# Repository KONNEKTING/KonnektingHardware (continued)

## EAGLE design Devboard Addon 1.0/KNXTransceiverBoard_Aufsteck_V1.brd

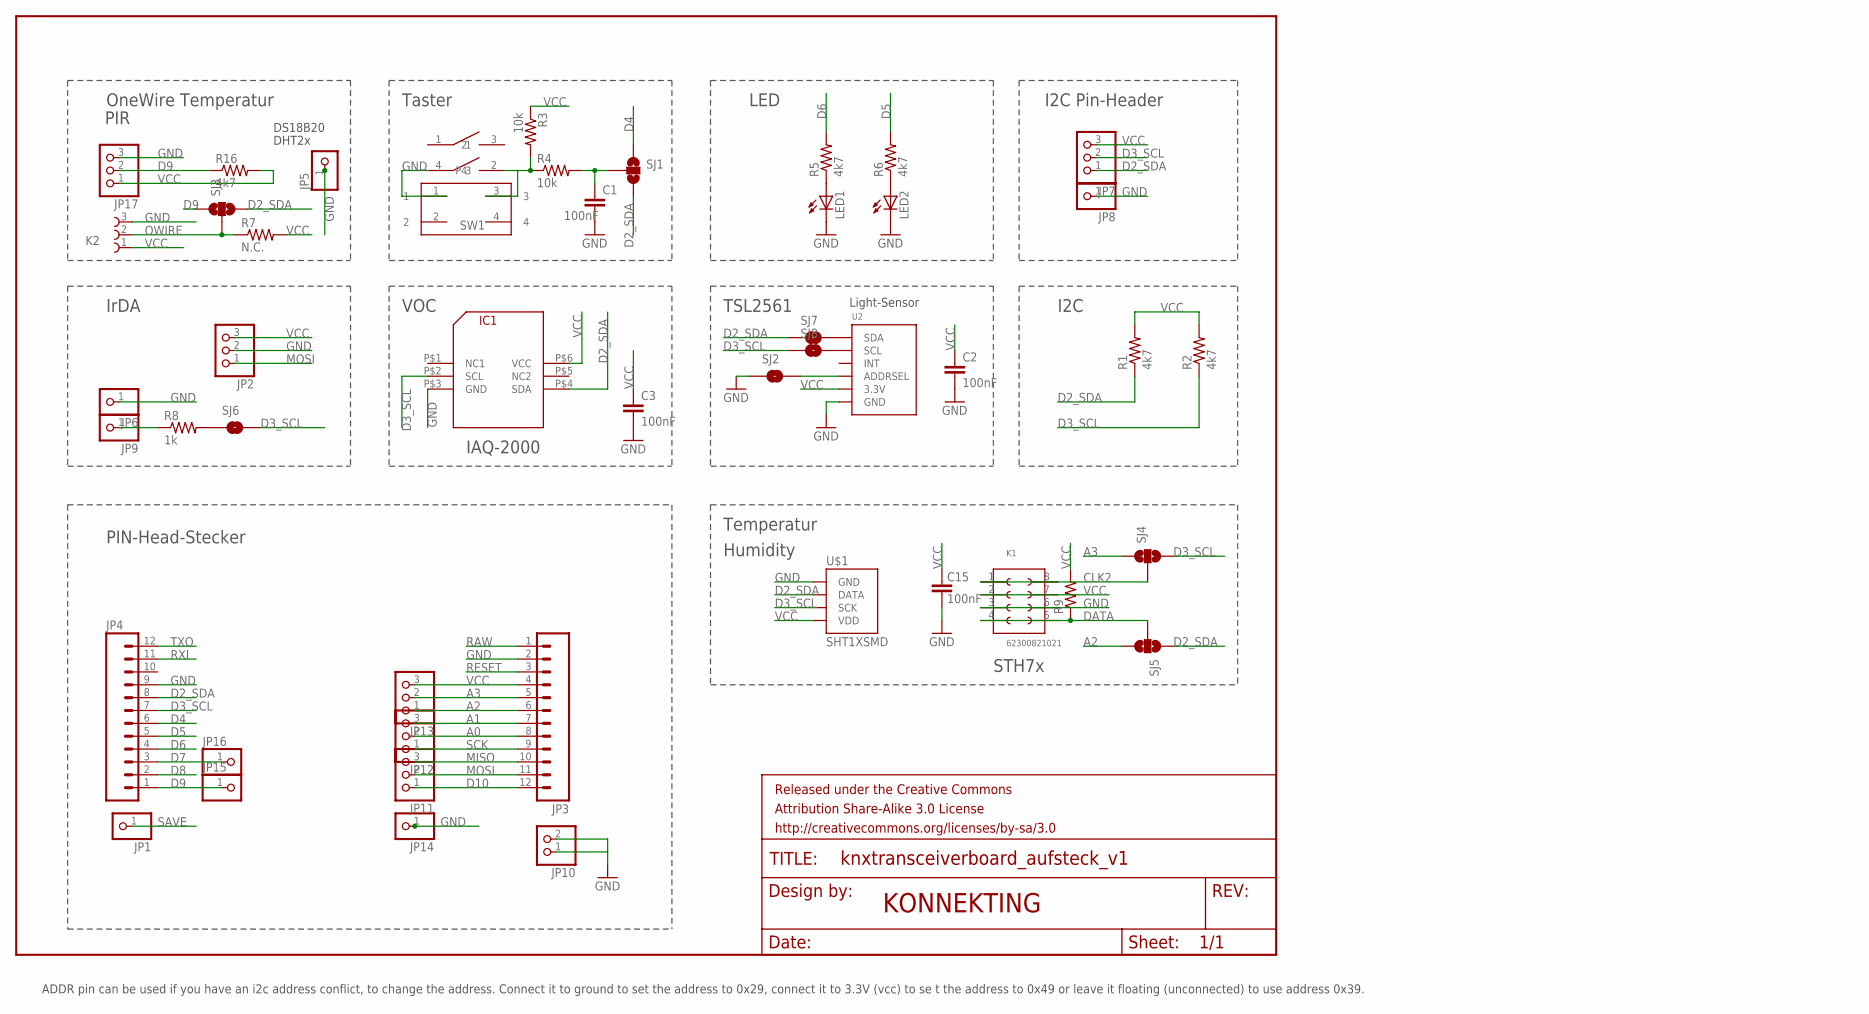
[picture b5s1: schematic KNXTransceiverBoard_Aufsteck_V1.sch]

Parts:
C1, C2, C3: 100nF; C0603
C15: 100nF; 0603-CAP
FRAME1: FRAME-LETTER; CREATIVE_COMMONS
IC1: AMSVOC
JP1, JP5, JP6, JP8, JP9, JP14, JP15, JP16: PINHD-1X1; 1X01
JP2, JP7, JP11, JP12, JP13, JP17: PINHD-1X3; 1X03
JP3, JP4: M12PTH; 1X12
JP10: PINHD-1X2; 1X02
K1: 62300821021
K2: 691101710003
LED1, LED2: LEDCHIPLED_0805; CHIPLED_0805
R1, R2, R5, R6, R16: 4k7; 0603-RES
R3, R4: 10k; 0603-RES
R7: N.C.; 0603-RES
R8: 1k; 0603-RES
R9: RESISTOR0603-RES; 0603-RES
SJ1, SJ3, SJ4, SJ5: SOLDERJUMPER_2WAY-OLDS; SJ_3
SJ2, SJ6, SJ7, SJ8: SOLDERJUMPERNO; SJ_2S-NO
SW1: 430156095926
U2: TSL2561; TSL2561_FN
U$1: SHT1XSMD; SHT1X
U$2: TASTER

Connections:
A0: JP3.8, JP12.2
A1: JP3.7, JP12.3
A2: JP3.6, JP13.1, SJ5.3
A3: JP3.5, JP13.2, SJ4.1
CLK2: K1.1, K1.8, SJ4.2
D2_SDA: IC1.P$4 (SDA), JP4.8, JP7.1, R1.1, SJ1.3, SJ3.3, SJ5.1, SJ7.1, U$1.2 (DATA)
D3_SCL: IC1.P$2 (SCL), JP4.7, JP7.2, R2.1, SJ4.3, SJ6.2, SJ8.1, U$1.3 (SCK)
D4: JP4.6, SJ1.1
D5: JP4.5, R6.2
D6: JP4.4, R5.2
D7: JP4.3, JP16.1
D8: JP4.2
D9: JP4.1, JP15.1, JP17.2, R16.1, SJ3.1
D10: JP3.12, JP11.1
DATA: K1.4, K1.5, R9.1, SJ5.2
GND: C1.2, C2.2, C3.2, C15.1, IC1.P$3 (GND), JP2.2, JP3.2, JP4.9, JP5.1, JP6.1, JP8.1, JP10.1, JP10.2, JP14.1, JP17.3, K1.3, K1.6, K2.3, LED1.C, LED2.C, SJ2.1, SW1.1, U2.VSS (GND), U$1.1 (GND), U$2.4 (3)
MISO: JP3.10, JP11.3
MOSI: JP2.1, JP3.11, JP11.2
unnamed: R3.2, R4.1, SW1.3, U$2.2 (P4)
unnamed: C1.1, R4.2, SJ1.2
unnamed: LED1.A, R5.1
unnamed: LED2.A, R6.1
unnamed: JP9.1, R8.1
unnamed: R8.2, SJ6.1
unnamed: SJ7.2, U2.DATA (SDA)
unnamed: SJ8.2, U2.CLK (SCL)
unnamed: SJ2.2, U2.ADR (ADDRSEL)
OWIRE: K2.2, R7.1, SJ3.2
RAW: JP3.1
RESET: JP3.3
RXI: JP4.11
SAVE: JP1.1
SCK: JP3.9, JP12.1
TXO: JP4.12
VCC: C2.1, C3.1, C15.2, IC1.P$6 (VCC), JP2.3, JP3.4, JP7.3, JP13.3, JP17.1, K1.2, K1.7, K2.1, R1.2, R2.2, R3.1, R7.2, R9.2, R16.2, U2.VDD (3.3V), U$1.4 (VDD)

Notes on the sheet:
KONNEKTING
OneWire Temperatur
DS18B20
DHT2x
IrDA
I2C
LED
ADDR pin can be used if you have an i2c address conflict, to change the address. Connect it to ground to set the address to 0x29, connect it to 3.3V (vcc) to se t the address to 0x49 or leave it floating (unconnected) to use address 0x39.
TSL2561
Light-Sensor
PIR
I2C Pin-Header
Taster
PIN-Head-Stecker
STH7x
VOC
IAQ-2000
Temperatur
Humidity

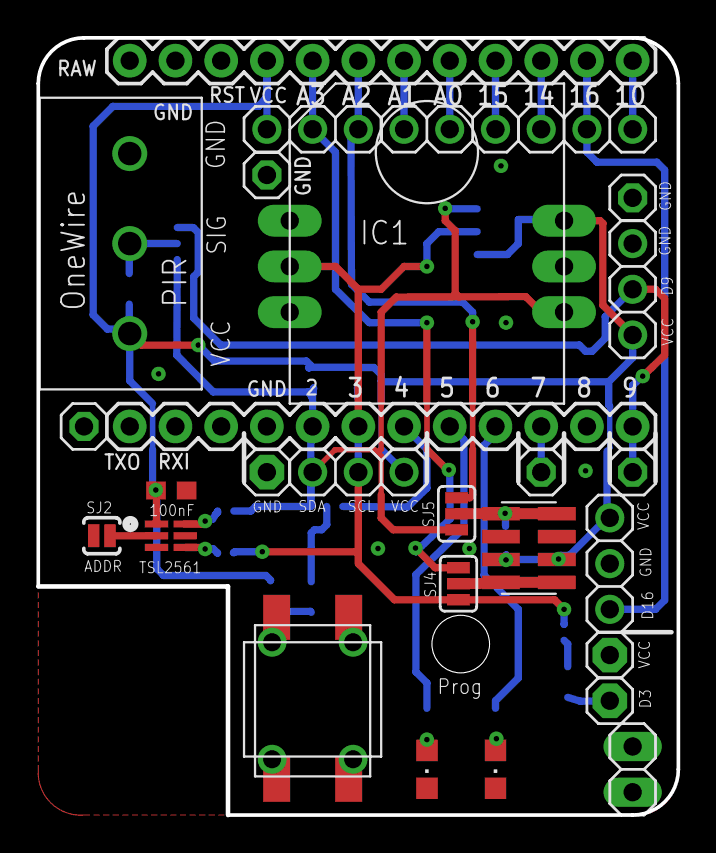
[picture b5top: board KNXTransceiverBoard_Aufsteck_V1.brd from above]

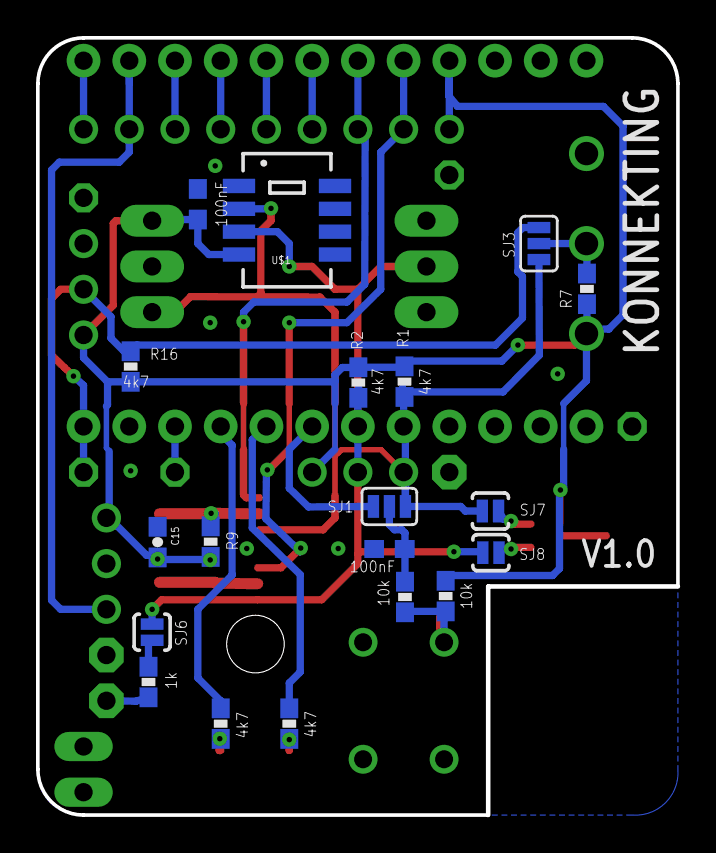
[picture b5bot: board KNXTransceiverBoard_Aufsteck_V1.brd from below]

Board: 2 copper layers, 35.6 x 43.2 mm, 49 parts (19 on the bottom side), 29 nets.

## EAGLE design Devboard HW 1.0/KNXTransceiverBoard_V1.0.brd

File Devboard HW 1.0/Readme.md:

# Devboard HW 1.0

HINWEISE BITTE BEACHTEN !!!

1. Wenn Ihr mit dem NCN5120 arbeitet, dann MÜSST ihr mit einem ProMini 3.3V 8Mhz arbeiten 
   -> Beim Flashen darauf achten das der "Programmer" welcher Art auch immer mit 3,3V arbeitet!
2. Wenn Ihr mit einer Siemens BCU arbeitet dann solltet ihr auch mit einem 3,3V Arduino arbeiten, 
   aber durch basteln kann man ihn auch mit 5V betreiben.

Wenn ihr auf dem HW1.0 mit einem ProMicro arbeiten wollt, dann müsst ihr das Pinout vom ProMini vergleichen, 
da der ProMicro nur einen RST-Pin besitzt. Am besten zwickt ihr den unterschiedliche Pin am ProMicro ab.

## License

Hardware and documentation released under this license: [license.md](/Devboard HW 1.0/license.md)

## More infos: 
[konnekting.de](http://www.konnekting.de/projekte/entwicklungsboards/)

## Parts

|Article number        | Part  | Description         | Amount      |
|:------------------|:---------|:--------------------|:-------------|
|	493-2203-1-ND	|	C11	|	CAP ALUM 100UF 20% 35V SMD	|	1	|
|	1276-1063-1-ND	|	C7	|	CAP CER 0.047UF 50V X7R 0603	|	1	|
|	399-7845-1-ND	|	C9	|	CAP CER 0.1UF 50V X7R 0603	|	1	|
|	490-9730-1-ND	|	C18;C20;C21	|	CAP CER 0.1UF 6.3V X7R 0603	|	3	|
|	1276-2407-1-ND	|	C15	|	CAP CER 10UF 6.3V X5R 0805	|	1	|
|	1276-1861-1-ND	|	C4	|	CAP CER 1UF 35V X5R 0603	|	1	|
|	399-7927-1-ND	|	C8	|	CAP CER 4700PF 25V X7R 0603	|	1	|
|	490-1198-1-ND	|	Y1	|	CER RES 16.0000MHZ 15PF SMD	|	1	|
|	36-1425-2-ND	|	Pins	|	CONN PC PIN CIRC 0.040DIA TIN	|	2	|
|	SS16T3GOSCT-ND	|	D1	|	DIODE SCHOTTKY 60V 1A SMA	|	1	|
|	SRR5028-221YCT-ND	|	L1	|	FIXED IND 220UH 300MA 1.25 OHM	|	1	|
|	NCN5120MNTWGOSCT-ND	|	NCN5120	|	IC RECEIVER/XMITTER KNX 40QFN	|	1	|
|	475-2815-1-ND	|	PROG_LED	|	LED BLUE DIFFUSED 0603 SMD	|	1	|
|	RNCP0603FTD1R00CT-ND	|	R3	|	RES SMD 1 OHM 1% 1/8W 0603	|	1	|
|	RNCP0603FTD100RCT-ND	|	R12_LED_3.3V	|	RES SMD 100 OHM 1% 1/8W 0603	|	1	|
|	RNCP0603FTD10K0CT-ND	|	R14	|	RES SMD 10K OHM 1% 1/8W 0603	|	1	|
|	311-1.00KHRCT-ND	|	R8;R9;R10	|	RES SMD 1K OHM 1% 1/10W 0603	|	3	|
|	A102515CT-ND	|	R1	|	RES SMD 22 OHM 5% 1W 2512	|	1	|
|	450-2146-1-ND	|	PROG_SW	|	SWITCH TACTILE SPST-NO 0.05A 24V	|	1	|
|	1SMA40CAT3GOSCT-ND	|	D2	|	TVS DIODE 40VWM 64.5VC SMA	|	1	|

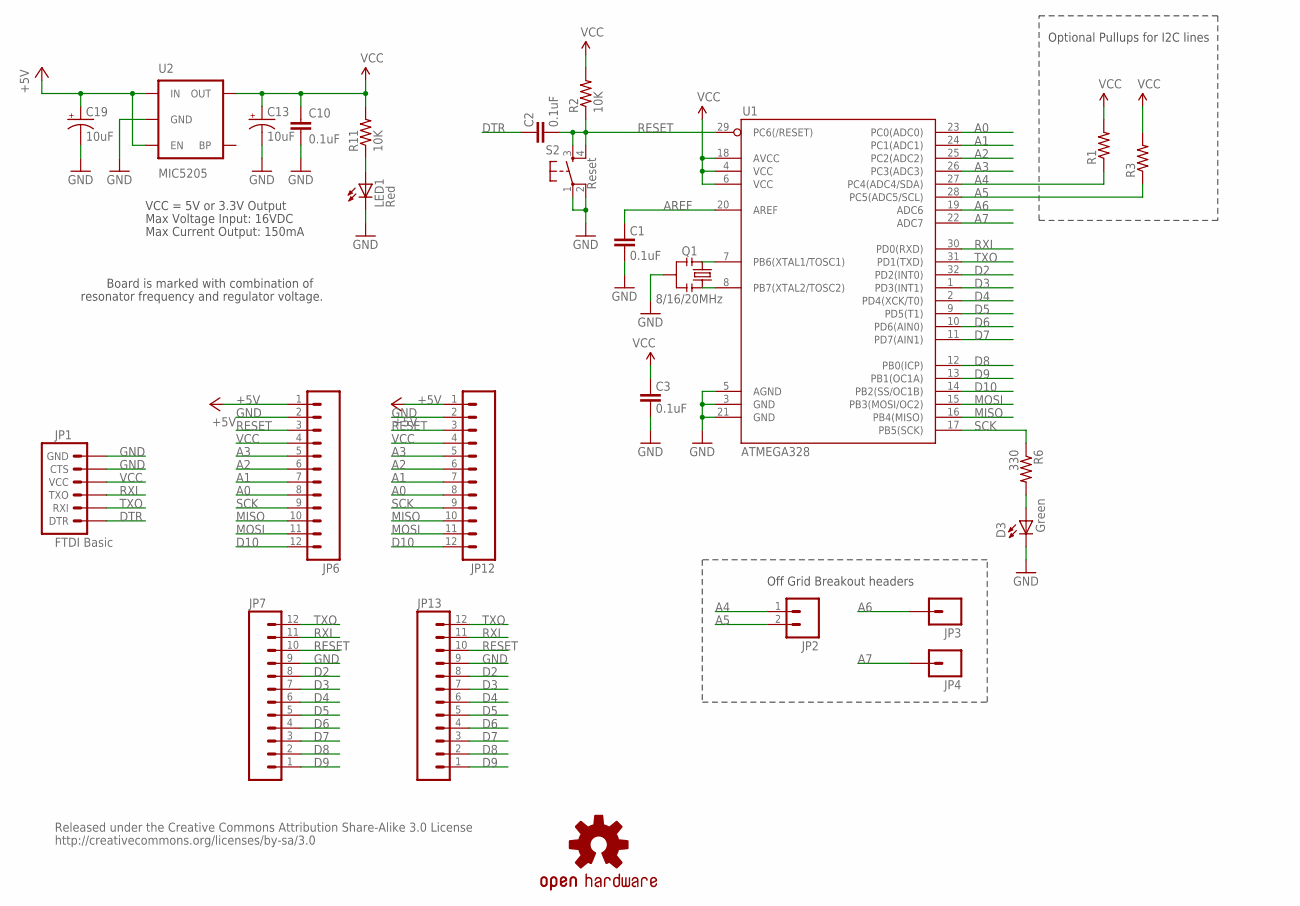
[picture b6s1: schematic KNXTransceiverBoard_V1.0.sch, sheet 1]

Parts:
C1, C2, C3, C10: 0.1uF; 0603-CAP
C13, C19: 10uF; EIA3216
D3: Green; LED-0603
JP1: FTDI Basic; 1X06
JP2: M02PTH; 1X02
JP3, JP4: M01PTH; 1X01
JP6, JP7, JP12, JP13: M12PTH; 1X12
LED1: Red; LED-0603
Q1: 8/16/20MHz; RESONATOR-SMD
R1, R3: RESISTOR0603-RES; 0603-RES
R2, R11: 10K; 0603-RES
R6: 330; 0603-RES
S2: Reset; TACTILE_SWITCH_SMD
U1: ATMEGA328; TQFP32-08
U2: MIC5205; SOT23-5
U$3: OSHW-LOGOS; OSHW-LOGO-S

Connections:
+5V: C19.A (+), JP6.1, JP12.1, U2.1 (IN), U2.3 (EN); also elsewhere on the board
A0: JP6.8, JP12.8, U1.23 (PC0(ADC0))
A1: JP6.7, JP12.7, U1.24 (PC1(ADC1))
A2: JP6.6, JP12.6, U1.25 (PC2(ADC2))
A3: JP6.5, JP12.5, U1.26 (PC3(ADC3))
A4: JP2.1, R1.1, U1.27 (PC4(ADC4/SDA))
A5: JP2.2, R3.1, U1.28 (PC5(ADC5/SCL))
A6: JP3.1, U1.19 (ADC6)
A7: JP4.1, U1.22 (ADC7)
AREF: C1.2, U1.20 (AREF)
D2: JP7.8, JP13.8, U1.32 (PD2(INT0)); also elsewhere on the board
D3: JP7.7, JP13.7, U1.1 (PD3(INT1)); also elsewhere on the board
D4: JP7.6, JP13.6, U1.2 (PD4(XCK/T0))
D5: JP7.5, JP13.5, U1.9 (PD5(T1))
D6: JP7.4, JP13.4, U1.10 (PD6(AIN0))
D7: JP7.3, JP13.3, U1.11 (PD7(AIN1))
D8: JP7.2, JP13.2, U1.12 (PB0(ICP)); also elsewhere on the board
D9: JP7.1, JP13.1, U1.13 (PB1(OC1A))
D10: JP6.12, JP12.12, U1.14 (PB2(SS/OC1B))
DTR: C2.2, JP1.1 (DTR)
GND: C1.1, C3.1, C10.2, C13.C (-), C19.C (-), D3.C, JP1.5 (CTS), JP1.6 (GND), JP6.2, JP7.9, JP12.2, JP13.9, LED1.C, Q1.2, S2.1, S2.2, U1.3 (GND), U1.5 (AGND), U1.21 (GND), U2.2 (GND); also elsewhere on the board
MISO: JP6.10, JP12.10, U1.16 (PB4(MISO))
MOSI: JP6.11, JP12.11, U1.15 (PB3(MOSI/OC2))
unnamed: Q1.1, U1.8 (PB7(XTAL2/TOSC2))
unnamed: Q1.3, U1.7 (PB6(XTAL1/TOSC1))
unnamed: D3.A, R6.2
unnamed: LED1.A, R11.1
RESET: C2.1, JP6.3, JP7.10, JP12.3, JP13.10, R2.1, S2.3, S2.4, U1.29 (PC6(/RESET))
RXI: JP1.3 (TXO), JP7.11, JP13.11, U1.30 (PD0(RXD)); also elsewhere on the board
SCK: JP6.9, JP12.9, R6.1, U1.17 (PB5(SCK))
TXO: JP1.2 (RXI), JP7.12, JP13.12, U1.31 (PD1(TXD)); also elsewhere on the board
VCC: C3.2, C10.1, C13.A (+), JP1.4 (VCC), JP6.4, JP12.4, R1.2, R2.2, R3.2, R11.2, U1.4 (VCC), U1.6 (VCC), U1.18 (AVCC), U2.5 (OUT); also elsewhere on the board

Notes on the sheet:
Released under the Creative Commons Attribution Share-Alike 3.0 License
http://creativecommons.org/licenses/by-sa/3.0
Max Voltage Input: 16VDC
Max Current Output: 150mA
Board is marked with combination of
resonator frequency and regulator voltage.
VCC = 5V or 3.3V Output
Optional Pullups for I2C lines
Off Grid Breakout headers

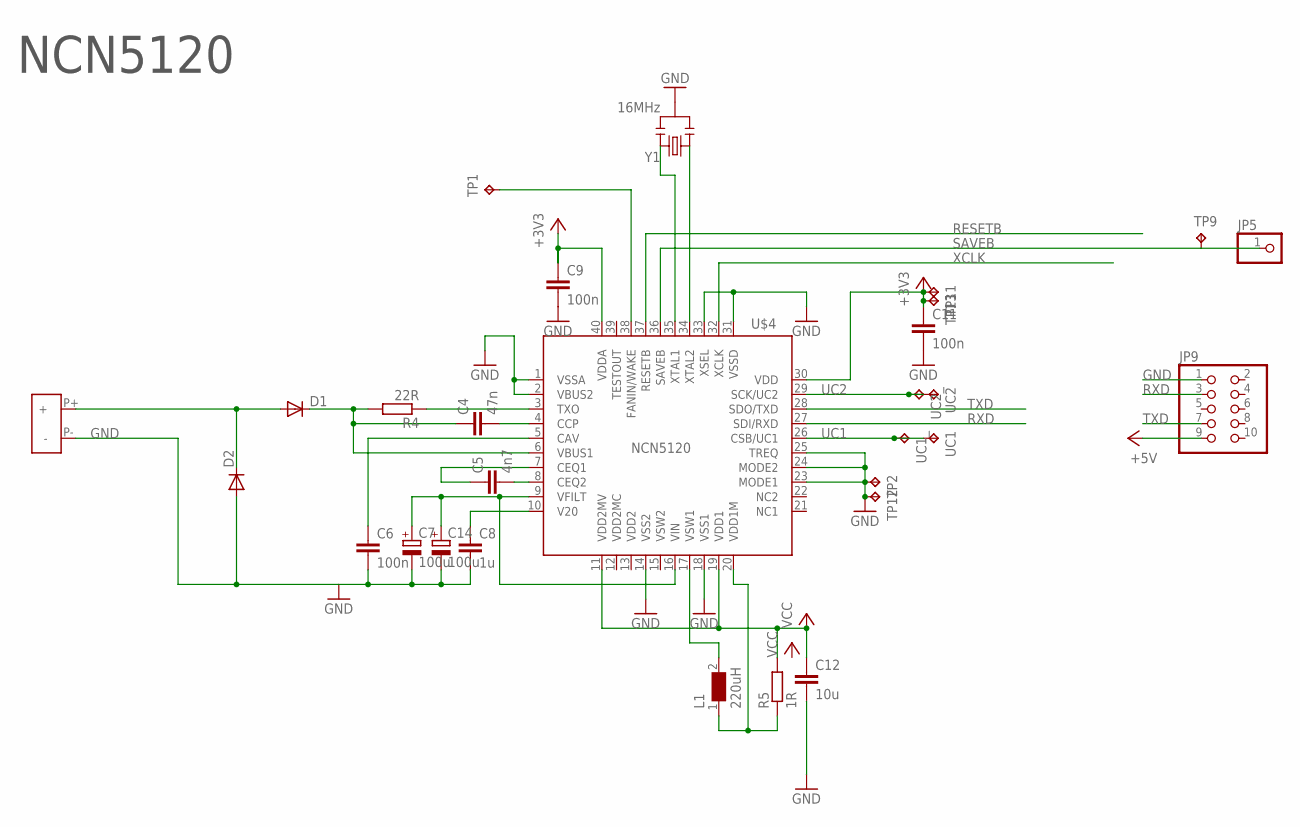
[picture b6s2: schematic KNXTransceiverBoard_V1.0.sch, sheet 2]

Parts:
C4: 47n; C0603
C5: 4n7; C0603
C6, C9, C11: 100n; C0603
C7, C14: 100u; SMC_D
C8: 1u; C0603
C12: 10u; C0805
D1, D2: DIODESMA-ALT; SMA-DIODE_ALT
JP5: PINHD-1X1; 1X01
JP9: PINHD-2X5; 2X05
L1: 220uH; WE-PD2_7850
R4: 22R; R2512
R5: 1R; R0603
TP1, TP9: TPTP10SQ; TP10SQ
TP2, TP11, TP12, TP13: TPTP09SQ; TP09SQ
U$2: KNX_KLEMME
U$4: NCN5120_KNX_TRANSCEIVER; QFN40
UC1, UC1_, UC2, UC2_: TPTP09SQ; TP09SQ
Y1: 16MHz; RESONATOR-SMD

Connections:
+5V: JP9.9; also elsewhere on the board
GND: C6.2, C7.-, C8.2, C9.2, C11.2, C12.2, C14.-, D2.A, JP9.1, TP2.TP, TP12.TP, U$2.P- (-), U$4.1 (VSSA), U$4.2 (VBUS2), U$4.14 (VSS2), U$4.18 (VSS1), U$4.23 (MODE1), U$4.24 (MODE2), U$4.25 (TREQ), U$4.31 (VSSD), U$4.33 (XSEL), Y1.2; also elsewhere on the board
unnamed: R4.1, U$4.3 (TXO)
unnamed: C4.1, D1.C, R4.2, U$4.6 (VBUS1)
unnamed: C5.1, U$4.7 (CEQ1)
unnamed: C7.+, C14.+, U$4.9 (VFILT), U$4.16 (VIN)
unnamed: C8.1, U$4.10 (V20)
unnamed: C6.1, U$4.5 (CAV)
unnamed: C4.2, U$4.4 (CCP)
unnamed: C5.2, U$4.8 (CEQ2)
unnamed: D1.A, D2.C, U$2.P+ (+)
unnamed: TP1.TP, U$4.38 (FANIN/WAKE)
unnamed: U$4.35 (XTAL1), Y1.3
unnamed: U$4.34 (XTAL2), Y1.1
unnamed: L1.2, U$4.17 (VSW1)
unnamed: L1.1, R5.1, U$4.20 (VDD1M)
RESETB: U$4.37 (RESETB)
RXD: JP9.3, U$4.27 (SDI/RXD); also elsewhere on the board
SAVEB: JP5.1, TP9.TP, U$4.36 (SAVEB)
TXD: JP9.7, U$4.28 (SDO/TXD); also elsewhere on the board
UC1: U$4.26 (CSB/UC1), UC1.TP, UC1_.TP
UC2: U$4.29 (SCK/UC2), UC2.TP, UC2_.TP
VCC: C9.1, C11.1, C12.1, R5.2, TP11.TP, TP13.TP, U$4.11 (VDD2MV), U$4.19 (VDD1), U$4.30 (VDD), U$4.40 (VDDA); also elsewhere on the board
XCLK: U$4.32 (XCLK)

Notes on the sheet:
NCN5120

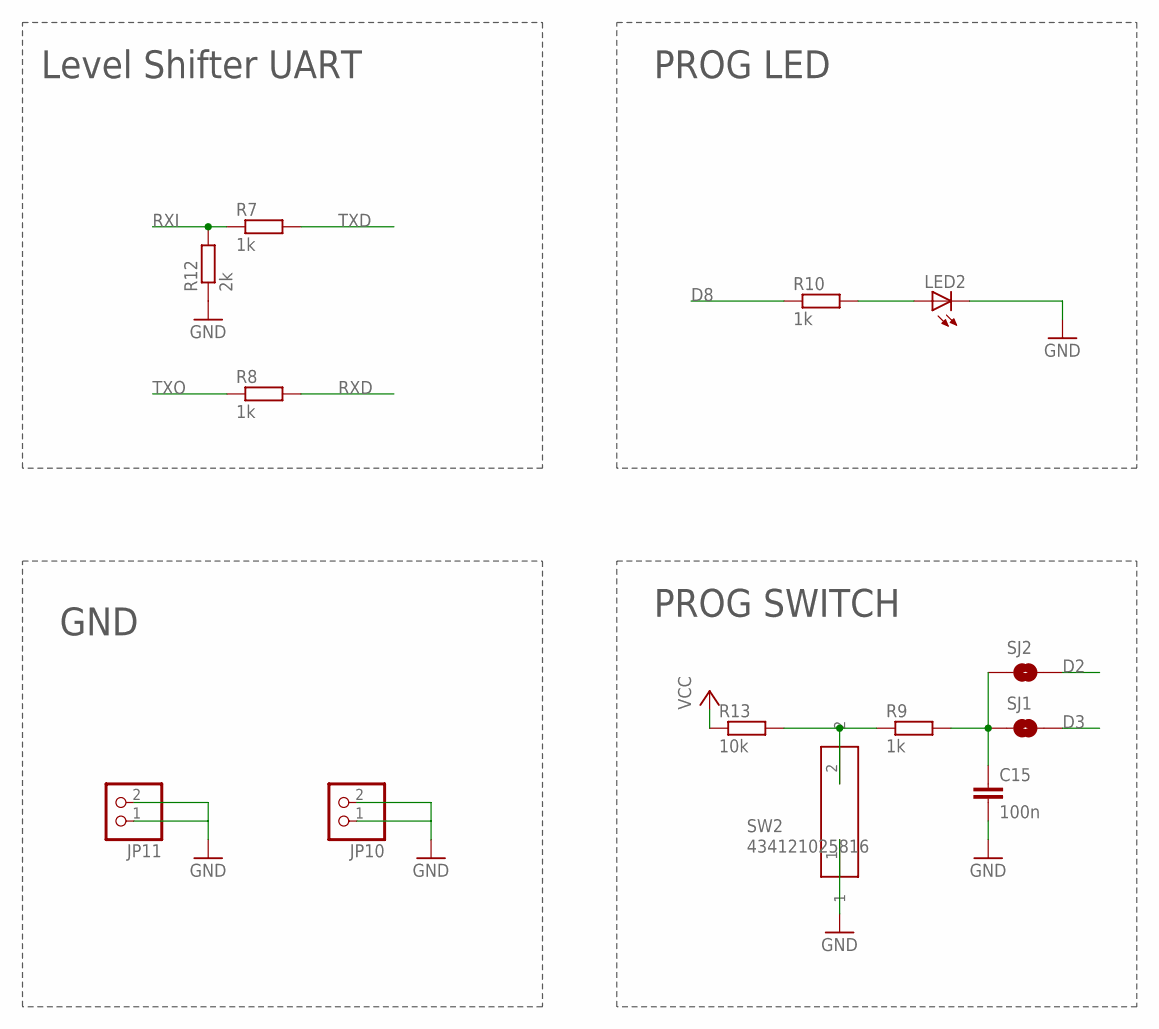
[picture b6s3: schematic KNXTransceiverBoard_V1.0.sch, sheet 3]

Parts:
C15: 100n; C0603
JP10, JP11: PINHD-1X2; 1X02
LED2: LEDCHIP-LED0805; CHIP-LED0805
R7, R8, R9, R10: 1k; R0603
R12: 2k; R0805
R13: 10k; R0603
SJ1, SJ2: Closed for 5V Board; SJ_2S
SW2: 434121025816

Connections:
D2: SJ2.2; also elsewhere on the board
D3: SJ1.2; also elsewhere on the board
D8: R10.1; also elsewhere on the board
GND: C15.2, JP10.1, JP10.2, JP11.1, JP11.2, LED2.C, R12.1, SW2.1; also elsewhere on the board
unnamed: R9.1, R13.2, SW2.2
unnamed: LED2.A, R10.2
PROG_SW: C15.1, R9.2, SJ1.1, SJ2.1
RXD: R8.2; also elsewhere on the board
RXI: R7.1, R12.2; also elsewhere on the board
TXD: R7.2; also elsewhere on the board
TXO: R8.1; also elsewhere on the board
VCC: R13.1; also elsewhere on the board

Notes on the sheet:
Level Shifter UART
PROG LED
GND
PROG SWITCH

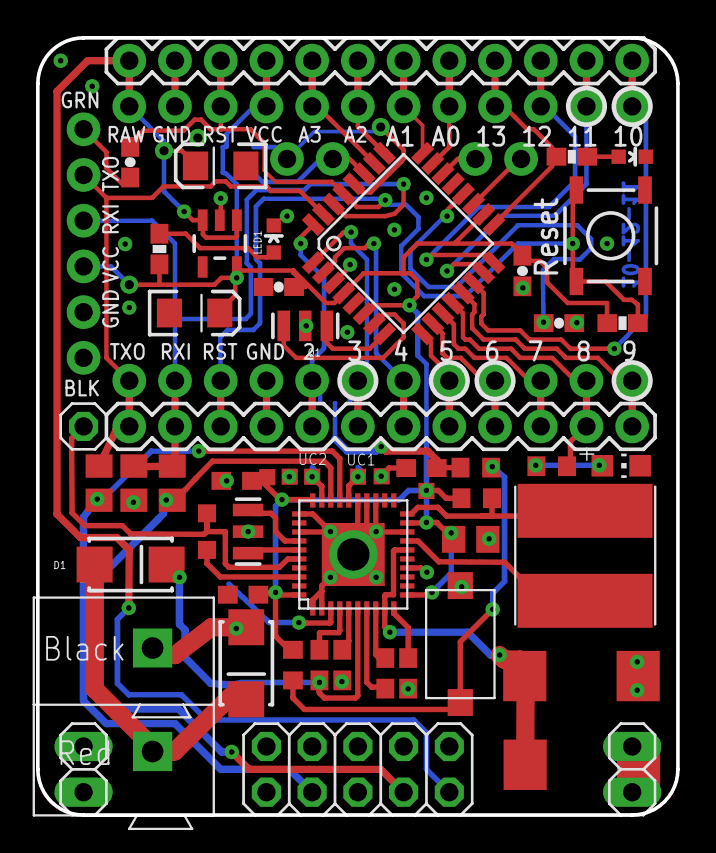
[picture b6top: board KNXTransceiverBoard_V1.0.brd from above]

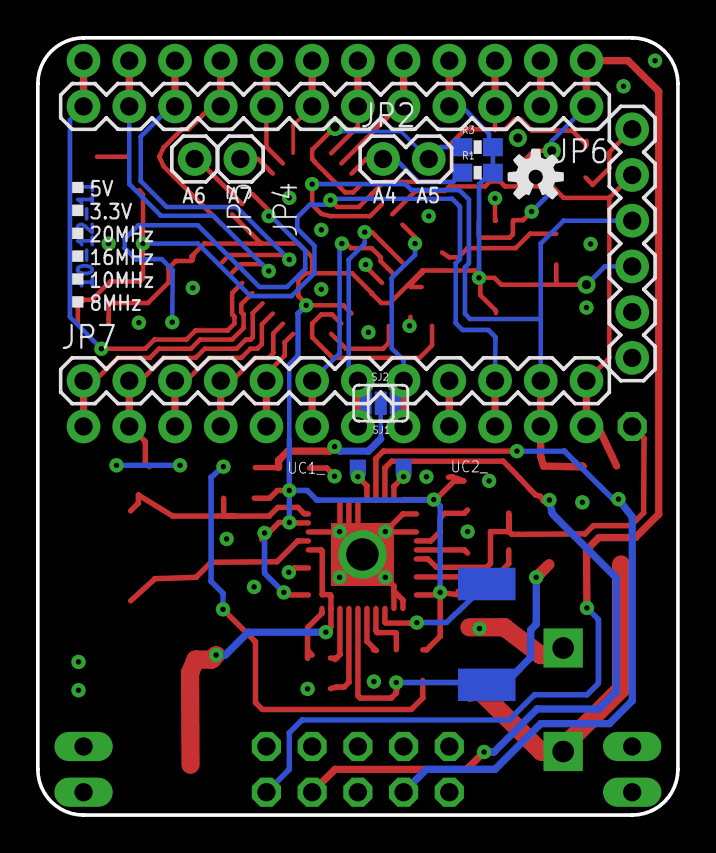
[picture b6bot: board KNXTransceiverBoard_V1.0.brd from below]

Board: 2 copper layers, 35.6 x 43.2 mm, 68 parts (14 on the bottom side), 54 nets.

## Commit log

2015-12-17 added license information
2016-03-01 initial commit of devboard/addon schematic+pcb data
2016-04-20 New revision
    New revision
2016-07-26 initial release
2016-07-27 schematic added
2016-07-27 license added
2016-07-27 BOM added
2016-07-31 Added board description
2016-08-02 english description added
2016-10-17 UFI PCB Eagle files added
2017-02-08 readme created
    readme with BOM
2017-08-20 MicroBCU and MI added
    MicroBCU R1.1
    MultiInterface R1.0
2017-12-03 Multi Interface Eagle Library
2017-12-13 Multi Interface EAGLE files
2018-02-21 MicroBCU R1.2
2018-08-26 R1.2
2018-08-26 R1.2 schematic
2021-05-10 neues sensormodul
